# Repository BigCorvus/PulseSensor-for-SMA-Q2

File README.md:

# PulseSensor-for-SMA-Q2
The Pulse Sensor from https://pulsesensor.com re-designed to be made on a tiny flex PCB to replace the HR sensor of  the SMA-Q2 watch.
Have the board manufactured via the OSHpark flex sevice. This way the board remains as low profile as possible. As a light shield to avoid light hitting the ADPS-9008 from the sides I used a piece of the black component tape the SC70-5 style opamp came packaged in. Just had to cafully cut out the bottom of the tiny tray et voila! This is usable for PPG acquisition from the wrist, although the peaks are less pronounced than on the fingertips. I ended up using higher value current limiting resistors for the LEDs, something around 1.2 kohm seemed more reasonable since otherwise the sensor was overwhelmed. This also limits the overall current consumption of the sensor to about 1mA. The LED current limiting resistor value probably also depends on skin color.

Note: the board version depicted on the photos is an older revision where I placed the wire pads wrong.

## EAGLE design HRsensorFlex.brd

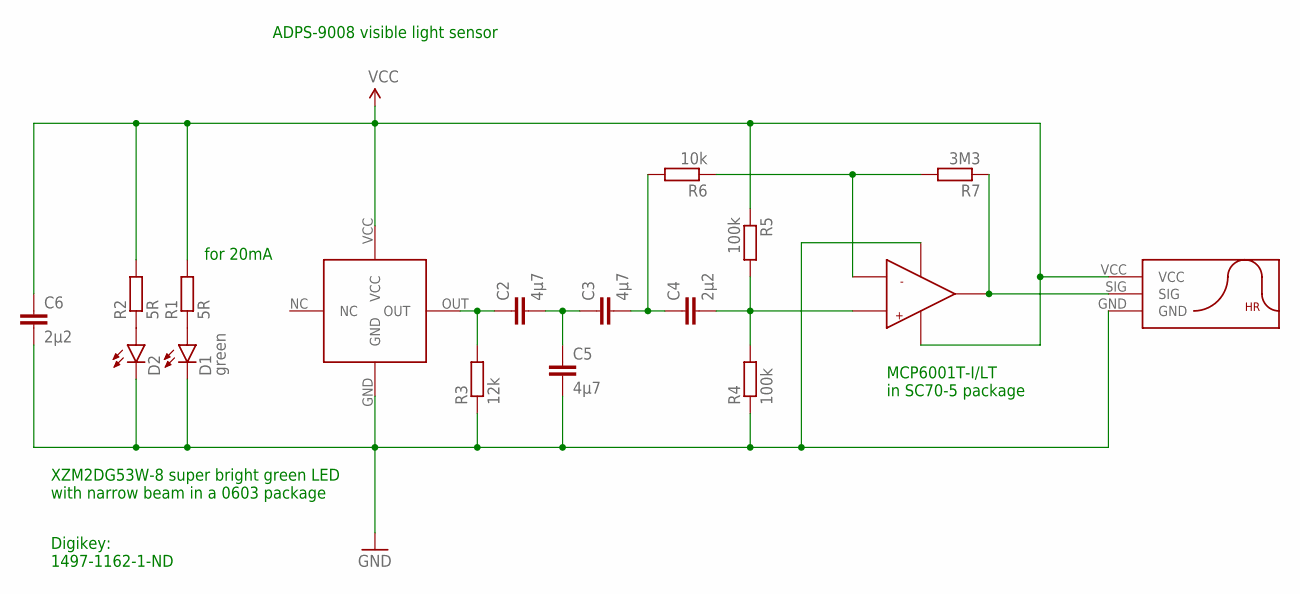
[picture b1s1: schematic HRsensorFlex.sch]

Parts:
C2, C3, C5: 4µ7; C0402
C4, C6: 2µ2; C0402
D1: green; LED-0603
D2: LED0603; LED-0603
R1, R2: 5R; R0402
R3: 12k; R0402
R4, R5: 100k; R0402
R6: 10k; R0402
R7: 3M3; R0402
U$1: MCP6001; SC70-5L
U$2: APDS-9008; APDS9008
U$3: HR_PADS

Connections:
GND: C5.2, C6.2, D1.C, D2.C, R3.1, R4.1, U$1.2 (VSS), U$2.GND, U$3.GND
IN+: C4.2, R4.2, R5.2, U$1.3 (+)
IN-: R6.1, R7.2, U$1.4 (-)
unnamed: D1.A, R1.1
unnamed: D2.A, R2.1
unnamed: C3.2, C4.1, R6.2
unnamed: C2.1, R3.2, U$2.OUT
unnamed: C2.2, C3.1, C5.1
OUT: R7.1, U$1.1 (OUT), U$3.SIG
VCC: C6.1, R1.2, R2.2, R5.1, U$1.5 (VDD), U$2.VCC, U$3.VCC

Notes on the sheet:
for 20mA
ADPS-9008 visible light sensor
XZM2DG53W-8 super bright green LED with narrow beam in a 0603 package
Digikey: 1497-1162-1-ND
MCP6001T-I/LT in SC70-5 package

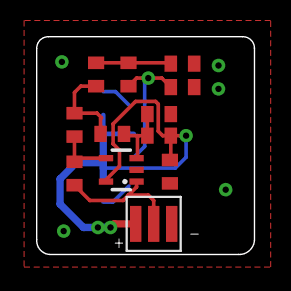
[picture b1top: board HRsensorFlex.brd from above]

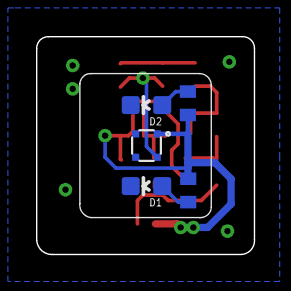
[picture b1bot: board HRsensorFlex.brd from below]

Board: 2 copper layers, 12.1 x 12.1 mm, 17 parts (5 on the bottom side), 10 nets.

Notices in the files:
parts and their libraries:
SparkFun-LED: Licensing: Creative Commons ShareAlike 4.0 International - https://creativecommons.org/licenses/by-sa/4.0
